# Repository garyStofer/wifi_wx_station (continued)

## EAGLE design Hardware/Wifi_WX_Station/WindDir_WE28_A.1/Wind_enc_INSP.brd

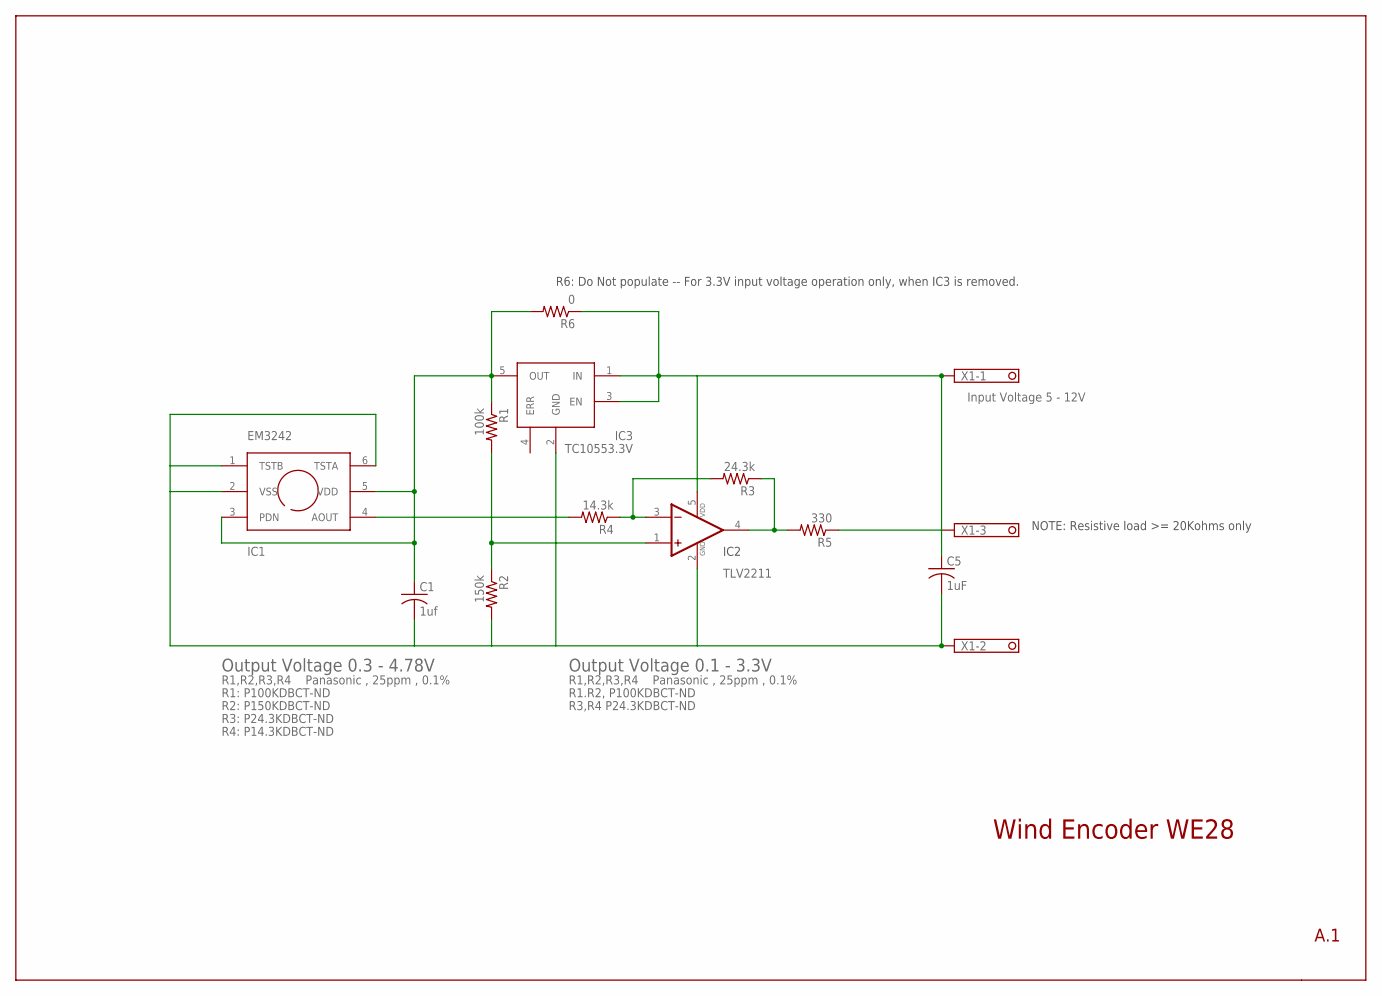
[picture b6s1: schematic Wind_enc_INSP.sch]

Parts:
C1: 1uf; C0805K
C5: 1uF; C0805K
IC1: EM3242; EM3242_SPECIAL
IC2: TLV2211; SOT23-5
IC3: TC10553.3V; SOT23-5
R1: 100k; R0603
R2: 150k; R0603
R3: 24.3k; R0603
R4: 14.3k; R0603
R5: 330; R0603
R6: 0; R0603
X1: 1751251

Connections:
unnamed: C5.1, IC2.5 (VDD), IC3.1 (IN), IC3.3 (EN), R6.1, X1.1
unnamed: C1.2, C5.2, IC1.1 (TSTB), IC1.2 (VSS), IC1.6 (TSTA), IC2.2 (VDD_GND), IC3.2 (GND), R2.2, X1.2
unnamed: R5.1, X1.3
unnamed: IC1.4 (AOUT), R4.2
unnamed: C1.1, IC1.3 (PDN), IC1.5 (VDD), IC3.5 (OUT), R1.1, R6.2
unnamed: IC2.3 (-IN), R3.2, R4.1
unnamed: IC2.4 (OUT), R3.1, R5.2
unnamed: IC2.1 (+IN), R1.2, R2.1

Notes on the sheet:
Wind Encoder WE28
IC2
R6: Do Not populate -- For 3.3V input voltage operation only, when IC3 is removed.
A.1
R1,R2,R3,R4 Panasonic , 25ppm , 0.1%
R2: P150KDBCT-ND
R1: P100KDBCT-ND
R3: P24.3KDBCT-ND
R4: P14.3KDBCT-ND
Output Voltage 0.3 - 4.78V
Input Voltage 5 - 12V
Output Voltage 0.1 - 3.3V
R1,R2,R3,R4 Panasonic , 25ppm , 0.1%
R1.R2, P100KDBCT-ND
R3,R4 P24.3KDBCT-ND
NOTE: Resistive load >= 20Kohms only

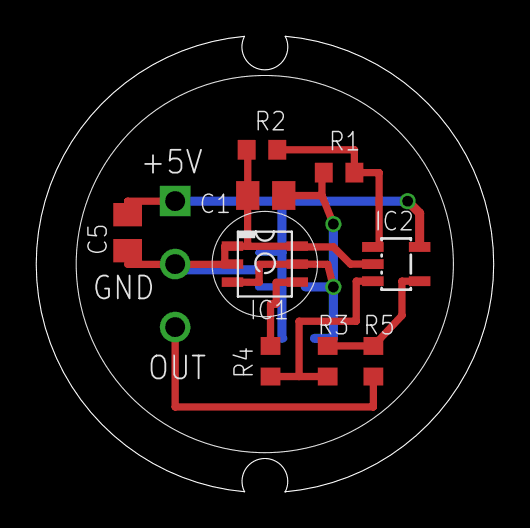
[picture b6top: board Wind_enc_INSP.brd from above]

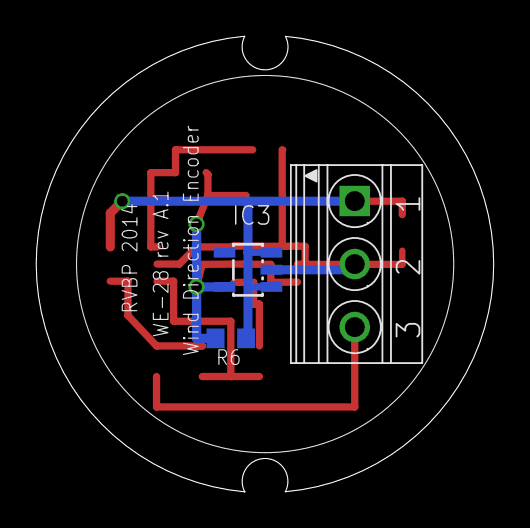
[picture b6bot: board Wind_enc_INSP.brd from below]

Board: 2 copper layers, 25.4 x 25.3 mm, 12 parts (3 on the bottom side), 8 nets.

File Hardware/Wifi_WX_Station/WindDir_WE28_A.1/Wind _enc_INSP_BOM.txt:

BOM for WE28-A1

OP-Amp 	TLV2211		DigiKey 	296-10501-1-ND	 
Encoder EM3242		Digikey  	974-1044-1-ND	 
VR 	TC10553.3V	DigiKey		TC10553.3VCT713CT-ND			 
R1 	100K 0.5% 25ppm 	 
R2	150K 0.1% 25ppm	 
R3	24.3k 0.1% 25ppm	 
R4 	14.3k 0.5% 25ppm	 
R5	330O 2%			 
C1,C2	1 uf/ 16V  			311-1457-1-ND

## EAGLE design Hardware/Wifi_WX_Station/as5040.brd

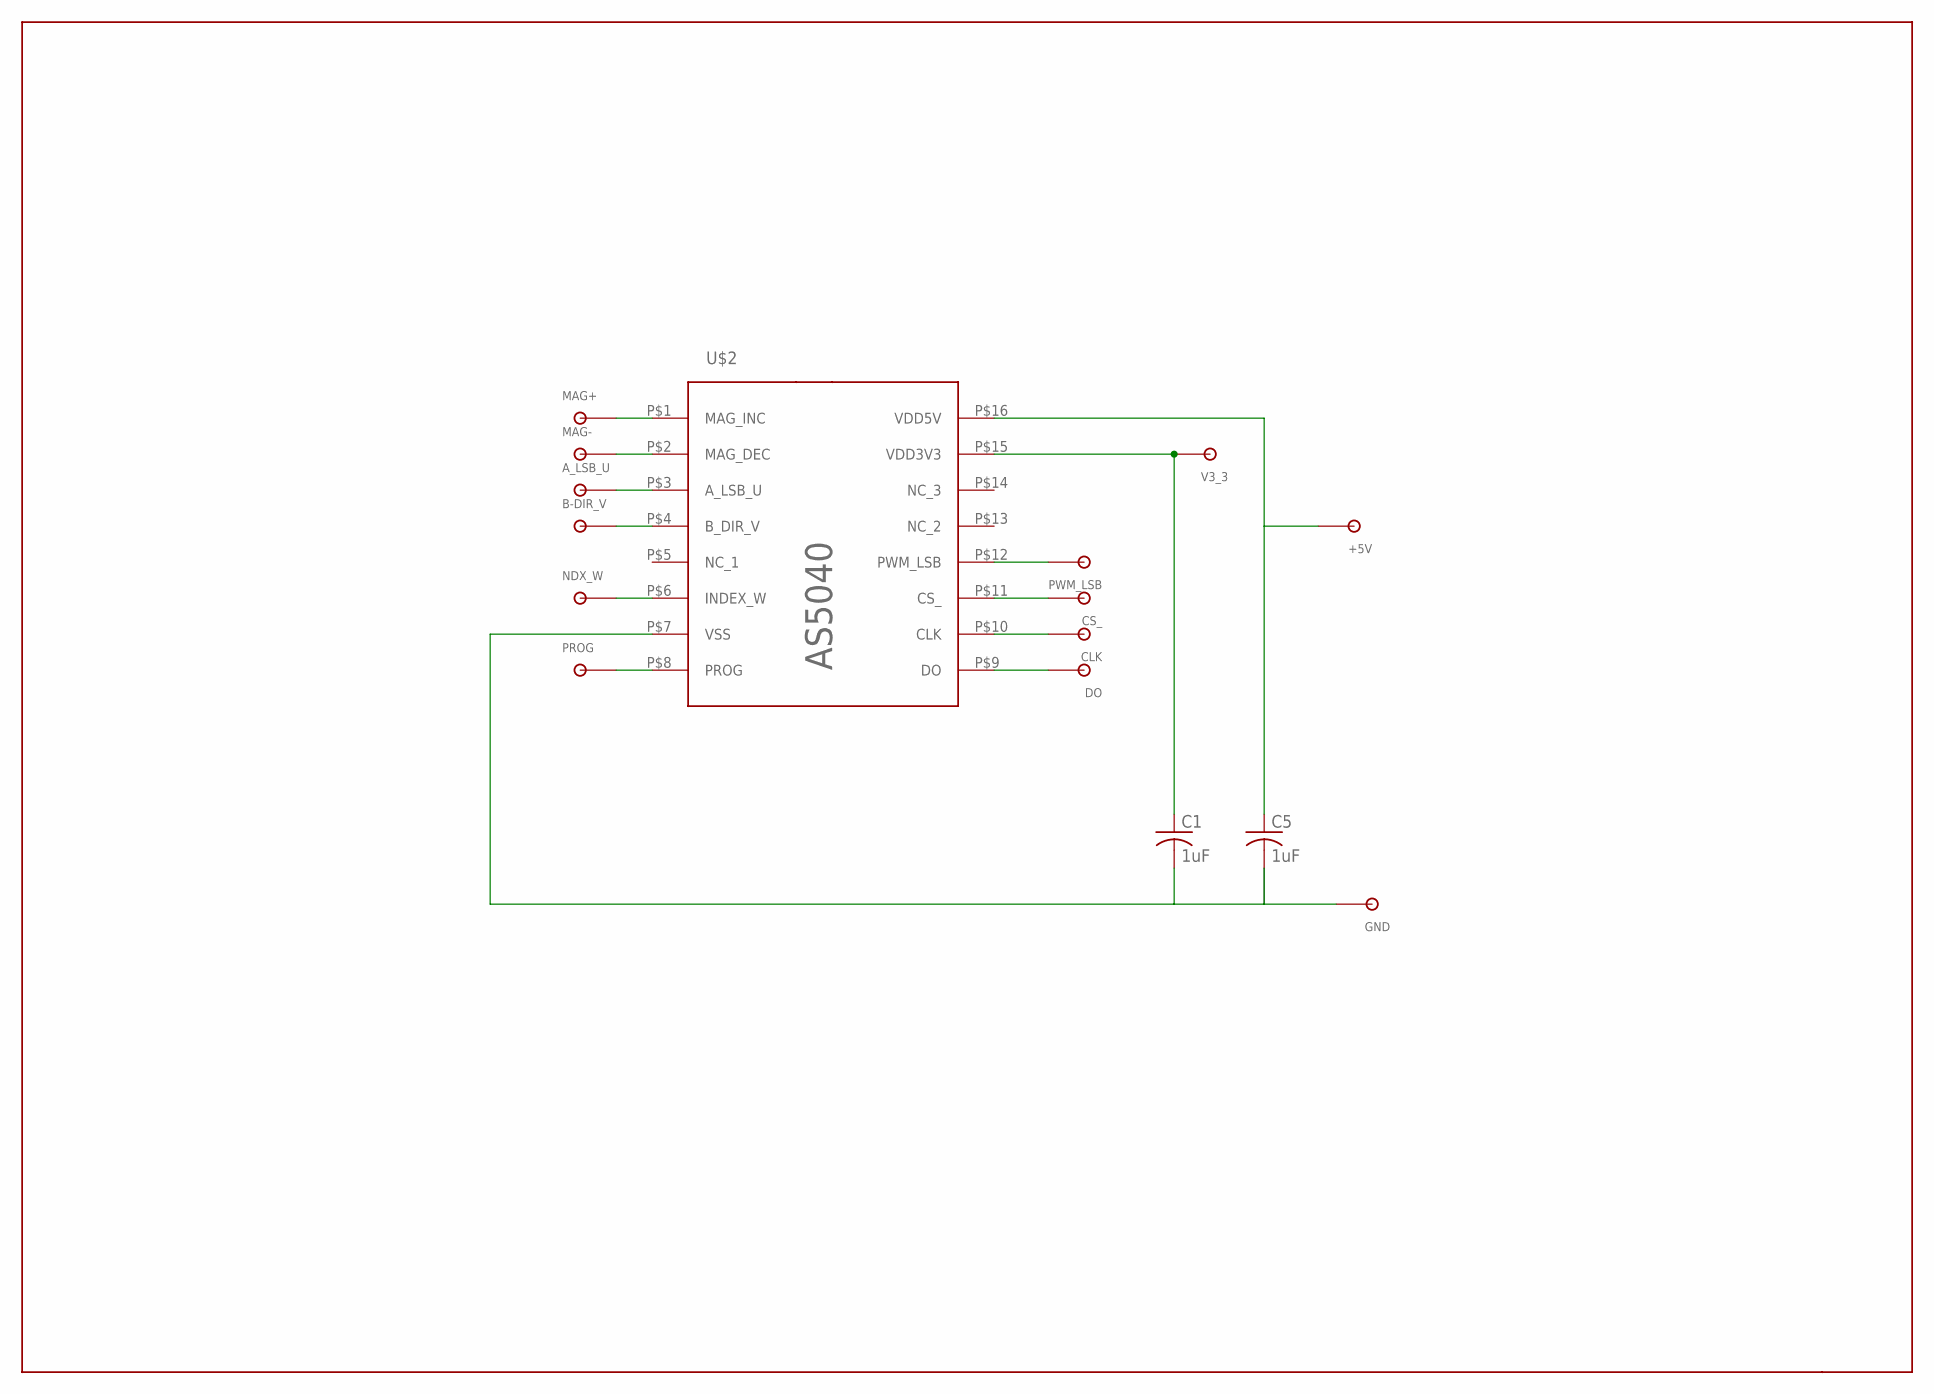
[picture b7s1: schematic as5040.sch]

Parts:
+5V: TPSOL; TP_SOL
A_LSB_U: TPSOL; TP_SOL
B-DIR_V: TPSOL; TP_SOL
C1, C5: 1uF; C0805K
CLK: TPSOL; TP_SOL
CS_: TPSOL; TP_SOL
DO: TPSOL; TP_SOL
GND: TPSOL; TP_SOL
MAG+: TPSOL; TP_SOL
MAG-: TPSOL; TP_SOL
NDX_W: TPSOL; TP_SOL
PROG: TPSOL; TP_SOL
PWM_LSB: TPSOL; TP_SOL
U$2: AS5040; AMS_5040_SPECIAL
V3_3: TPSOL; TP_SOL

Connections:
unnamed: C1.2, C5.2, GND.P$1, U$2.P$7 (VSS)
unnamed: +5V.P$1, C5.1, U$2.P$16 (VDD5V)
unnamed: C1.1, U$2.P$15 (VDD3V3), V3_3.P$1
unnamed: MAG+.P$1, U$2.P$1 (MAG_INC)
unnamed: MAG-.P$1, U$2.P$2 (MAG_DEC)
unnamed: A_LSB_U.P$1, U$2.P$3 (A_LSB_U)
unnamed: B-DIR_V.P$1, U$2.P$4 (B_DIR_V)
unnamed: NDX_W.P$1, U$2.P$6 (INDEX_W)
unnamed: PROG.P$1, U$2.P$8 (PROG)
unnamed: PWM_LSB.P$1, U$2.P$12 (PWM_LSB)
unnamed: CS_.P$1, U$2.P$11 (CS_)
unnamed: CLK.P$1, U$2.P$10 (CLK)
unnamed: DO.P$1, U$2.P$9 (DO)

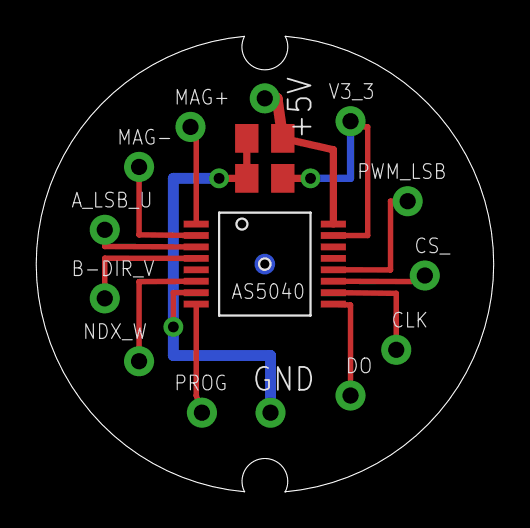
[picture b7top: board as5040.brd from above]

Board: 2 copper layers, 25.4 x 25.3 mm, 16 parts (0 on the bottom side), 13 nets.

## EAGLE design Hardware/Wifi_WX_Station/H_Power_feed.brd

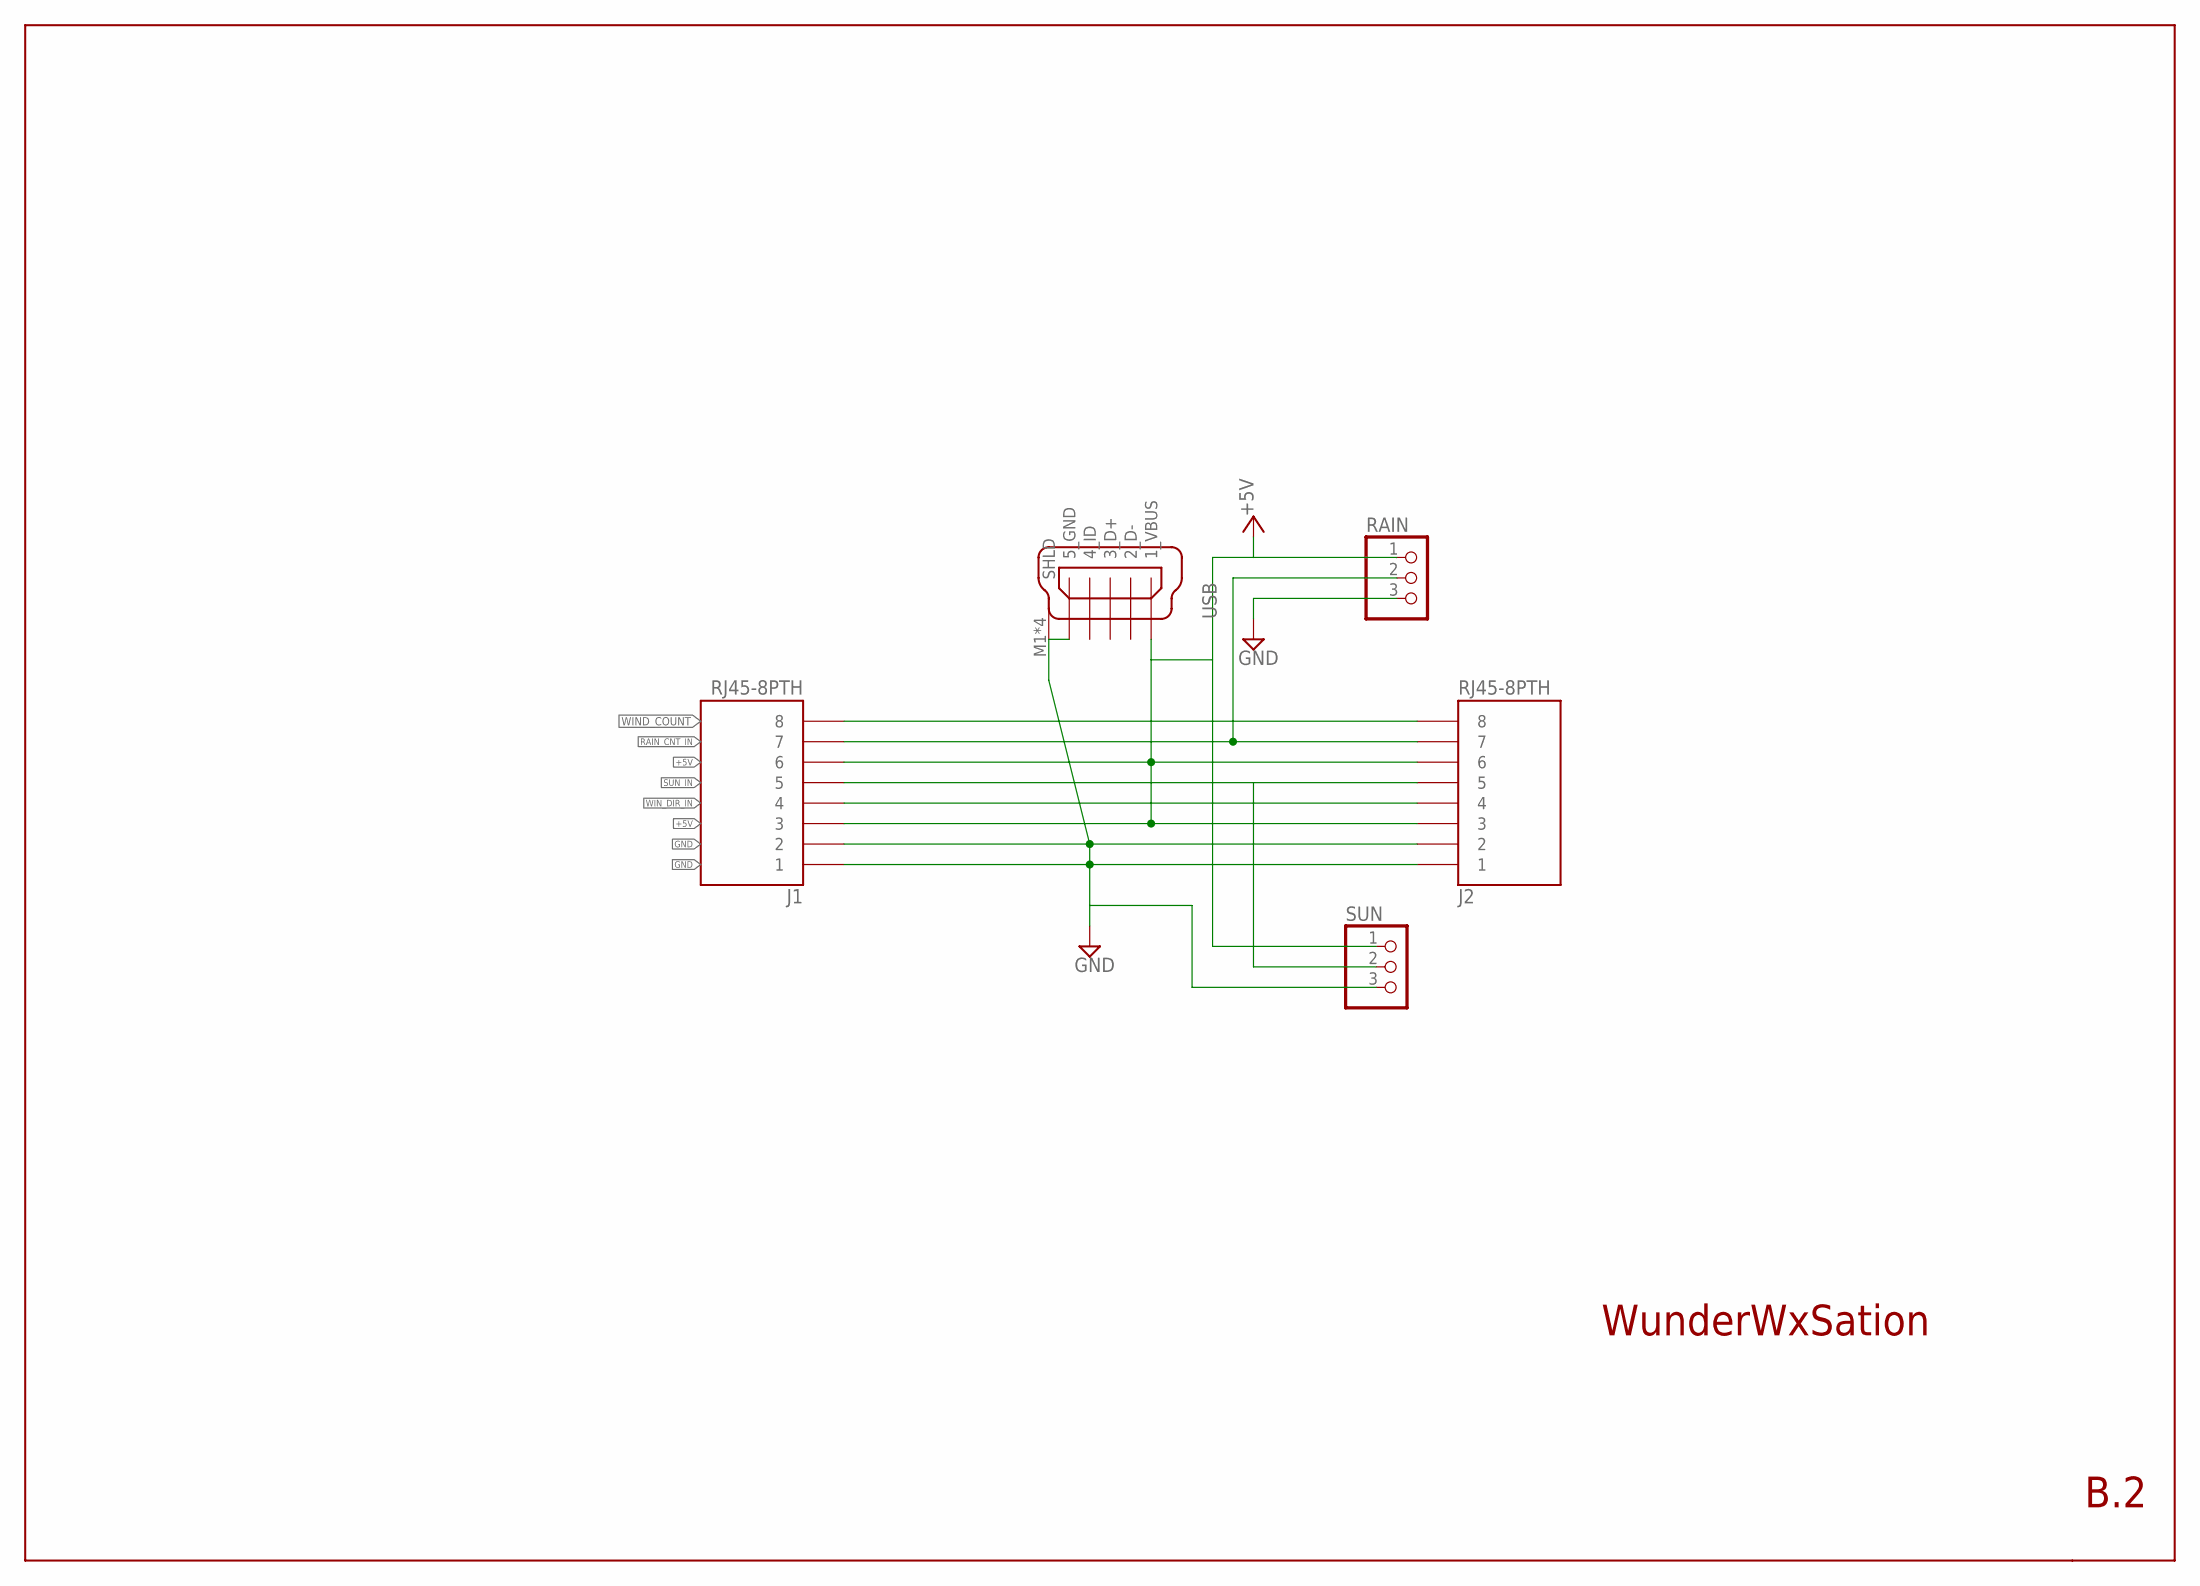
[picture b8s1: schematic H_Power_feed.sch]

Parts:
J1, J2: RJ45-8PTH; RJ45-8
RAIN: PINHD-1X3MOLEX_KK; 1X3_MOLEX_KK
SUN: PINHD-1X3MOLEX_KK; 1X3_MOLEX_KK
USB: MINI-USB-32005-301; 32005-301

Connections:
+5V: J1.3, J1.6, J2.3, J2.6, RAIN.1, SUN.1, USB.1_VBUS
GND: J1.1, J1.2, J2.1, J2.2, RAIN.3, SUN.3, USB.5_USB_GND (5_GND), USB.M1 (SHLD), USB.M2 (SHLD), USB.M3 (SHLD), USB.M4 (SHLD)
RAIN_CNT_IN: J1.7, J2.7, RAIN.2
SUN_IN: J1.5, J2.5, SUN.2
WIND_COUNT: J1.8, J2.8
WIN_DIR_IN: J1.4, J2.4

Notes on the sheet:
WunderWxSation
B.2

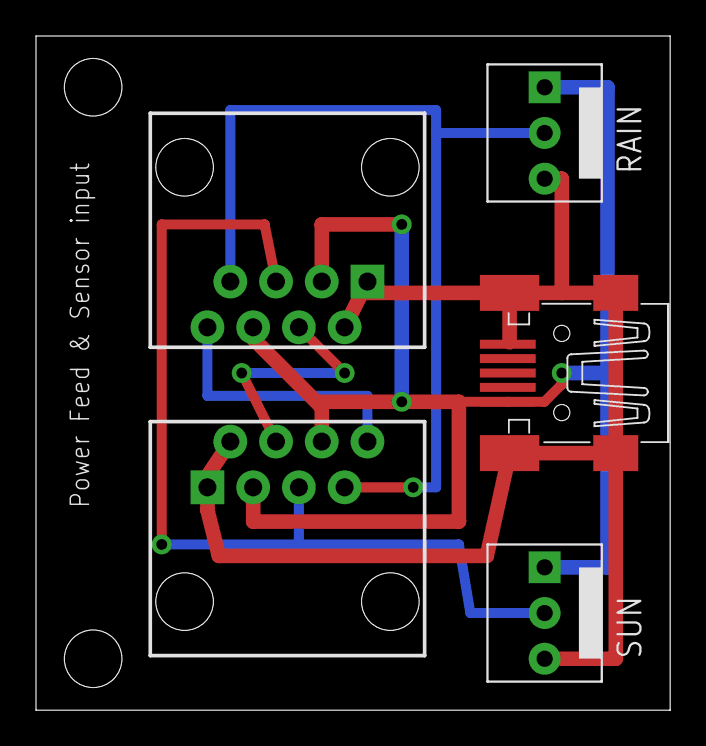
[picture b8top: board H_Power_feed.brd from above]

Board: 2 copper layers, 35.2 x 37.5 mm, 5 parts (0 on the bottom side), 6 nets.

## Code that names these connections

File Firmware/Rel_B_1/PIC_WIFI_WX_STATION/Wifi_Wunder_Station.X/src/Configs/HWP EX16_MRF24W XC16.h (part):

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#define All_LEDS_off()                 LATA = 0
// Momentary push buttons
#define BUTTON0_TRIS		(TRISDbits.TRISD13)	// Ref S4
#define	BUTTON0_IO			(PORTDbits.RD13)
#define BUTTON1_TRIS		(TRISAbits.TRISA7)	// Ref S5;  Note: This is multiplexed with LED7
#define	BUTTON1_IO			(PORTAbits.RA7)
#define BUTTON2_TRIS		(TRISDbits.TRISD7)	// Ref S6
#define	BUTTON2_IO			(PORTDbits.RD7)
#define BUTTON3_TRIS		(TRISDbits.TRISD6)	// Ref S3
#define	BUTTON3_IO			(PORTDbits.RD6)

#define BARO_CS_TRIS   ( TRISGbits.TRISG0)
#define BARO_CS_IO     ( LATGbits.LATG0)
#define UART2TX_TRIS			(TRISFbits.TRISF5)
#define UART2TX_IO			(PORTFbits.RF5)
#define UART2RX_TRIS			(TRISFbits.TRISF4)
#define UART2RX_IO			(PORTFbits.RF4)

//// ENC28J60 I/O pins
//#if defined(__PIC24FJ256GA110__) || defined(__dsPIC33E__)|| defined(__PIC24E__)	// PIC24FJ256GA110 must place the ENC28J60 on SPI2 because PIC rev A3 SCK1 output pin is a PPS input only (fixed on A5, but demos use SPI2 for simplicity)
//	#define ENC_CS_TRIS			(TRISFbits.TRISF12)	// Comment this line out if you are using the ENC424J600/624J600, MRF24W, or other network controller.
//	#define ENC_CS_IO			(LATFbits.LATF12)
//	// SPI SCK, SDI, SDO pins are automatically controlled by the 
//	// PIC24/dsPIC SPI module 
//	#define ENC_SPI_IF			(IFS2bits.SPI2IF)
//	#define ENC_SSPBUF			(SPI2BUF)
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//#else	// SPI1 for all other processors
//	#define ENC_CS_TRIS			(TRISDbits.TRISD14)	// Comment this line out if you are using the ENC424J600/624J600, MRF24W, or other network controller.
//	#define ENC_CS_IO			(LATDbits.LATD14)
//	// SPI SCK, SDI, SDO pins are automatically controlled by the 
//	// PIC24/dsPIC SPI module 
//	#define ENC_SPI_IF			(IFS0bits.SPI1IF)
//	#define ENC_SSPBUF			(SPI1BUF)
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//	#define ENC100_INT_IO				(PORTAbits.RA13)
//#else
//	#define ENC100_INT_TRIS				(TRISEbits.TRISE9)		// INT signal is optional and currently unused in the Microchip TCP/IP Stack.  Leave this pin disconnected and comment out this pin definition if you don't want it.
//	#define ENC100_INT_IO				(PORTEbits.RE9)
//#endif
//#if (ENC100_INTERFACE_MODE >= 1)	// Parallel mode
//	// PSP control signal pinout
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//		// SPI2 CANNOT BE ENABLED WHEN ACCESSING THE ENC624J600 FOR THESE TWO MODES AS THE PINS OVERLAP WITH ADDRESS LINES.
//		#if defined(ENC100_PSP_USE_INDIRECT_RAM_ADDRESSING)	// Only ENC624J600 address pins A0-A8 connected (A9-A14 tied to Vdd)
//			#if defined(__PIC24FJ256GB210__)
//				#define ENC100_INIT_PSP_BIT_BANG()	do{ANSA &= 0xF9E7; ANSB &= 0x3FFF; ANSG &= 0xFCFF;} while(0)		// RE0-RE7, RF12, RD11, RD4, RD5 (AD0-AD7, A5, A8, WR, RD) pins are already digital only pins.
//			#else
//				#define ENC100_INIT_PSP_BIT_BANG()	do{((volatile unsigned char*)&AD1PCFGH)[1] = 0xFF; ((volatile unsigned char*)&AD1PCFGL)[1] |= 0xC0;}while(0)	// Disable AN24-AN31 and AN14-AN15 analog inputs on RE0-RE7 and RB14-RB15 pins (ENCX24J600 AD0-AD7, A1-A0)
//			#endif
//			#define ENC100_SET_ADDR_TRIS_OUT()	do{TRISA &= 0xF9E7; TRISB &= 0x3FFF; TRISFbits.TRISF12 = 0; TRISGbits.TRISG9 = 0; TRISDbits.TRISD11 = 0;}while(0)
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//			#define ENC100_SET_AD_IO(data)		(((volatile unsigned char*)&LATE)[0] = (unsigned char)(data))
//		#else 	// All ENC624J600 address pins A0-A14 connected
//			#if defined(__PIC24FJ256GB210__)
//				#define ENC100_INIT_PSP_BIT_BANG()	do{ANSA &= 0xF9E7; ANSB &= 0x03FF; ANSG &= 0xFCFF;} while(0)		// RE0-RE7, RF12, RD11, RD4, RD5 (AD0-AD7, A5, A14, WR, RD) pins are already digital only pins.
//			#else
//				#define ENC100_INIT_PSP_BIT_BANG()	do{((volatile unsigned char*)&AD1PCFGH)[1] = 0xFF; ((volatile unsigned char*)&AD1PCFGL)[1] |= 0xFC;}while(0)	// Disable AN24-AN31 and AN10-AN15 analog inputs on RE0-RE7 and RB10-RB15 pins (ENCX24J600 AD0-AD7, A1-A0, A13-A10)
//			#endif
//			#define ENC100_SET_ADDR_TRIS_OUT()	do{TRISA &= 0xF9E7; TRISB &= 0x03FF; TRISF &= 0xEFCF; TRISGbits.TRISG9 = 0; TRISDbits.TRISD11 = 0;}while(0)
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//			#define ENC100_WRH_B1SEL_IO			ENC100_SO_WR_B0SEL_EN_IO
//			#define ENC100_SET_AD_TRIS_IN()		do{((volatile unsigned char*)&TRISE)[0] = 0xFF; TRISAbits.TRISA15 = 1; TRISCbits.TRISC13 = 1; TRISD |= 0x30C0; TRISGbits.TRISG0 = 1; TRISGbits.TRISG1 = 1;}while(0)
//			#define ENC100_SET_AD_TRIS_OUT()	do{((volatile unsigned char*)&TRISE)[0] = 0x00; TRISAbits.TRISA15 = 0; TRISCbits.TRISC13 = 0; TRISD &= 0xCF3F; TRISGbits.TRISG0 = 0; TRISGbits.TRISG1 = 0;}while(0)
//			#define ENC100_GET_AD_IOH()			(PORTGbits.RG0 | (PORTGbits.RG1<<1) | (PORTCbits.RC13<<2) | (PORTAbits.RA15<<3) | (PORTDbits.RD12<<4) | (PORTDbits.RD13<<5) | (PORTDbits.RD6<<6) | (PORTDbits.RD7<<7))
//			#define ENC100_GET_AD_IOL()			(((volatile unsigned char*)&PORTE)[0])
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//			#define ENC100_SET_AD_IOL(data)		(((volatile unsigned char*)&LATE)[0] = (unsigned char)(data))
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//			#define ENC100_WRH_B1SEL_IO			ENC100_SO_WR_B0SEL_EN_IO
//			#define ENC100_SET_AD_TRIS_IN()		do{((volatile unsigned char*)&TRISE)[0] = 0xFF; TRISAbits.TRISA15 = 1; TRISCbits.TRISC13 = 1; TRISD |= 0x30C0; TRISGbits.TRISG0 = 1; TRISGbits.TRISG1 = 1;}while(0)
//			#define ENC100_SET_AD_TRIS_OUT()	do{((volatile unsigned char*)&TRISE)[0] = 0x00; TRISAbits.TRISA15 = 0; TRISCbits.TRISC13 = 0; TRISD &= 0xCF3F; TRISGbits.TRISG0 = 0; TRISGbits.TRISG1 = 0;}while(0)
//			#define ENC100_GET_AD_IOH()			(PORTGbits.RG0 | (PORTGbits.RG1<<1) | (PORTCbits.RC13<<2) | (PORTAbits.RA15<<3) | (PORTDbits.RD12<<4) | (PORTDbits.RD13<<5) | (PORTDbits.RD6<<6) | (PORTDbits.RD7<<7))
//			#define ENC100_GET_AD_IOL()			(((volatile unsigned char*)&PORTE)[0])
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//			#define ENC100_SET_AD_IOL(data)		(((volatile unsigned char*)&LATE)[0] = (unsigned char)(data))
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//	#elif ENC100_INTERFACE_MODE == 5 || ENC100_INTERFACE_MODE == 6	// Mutliplexed 8-bit address/data modes
//		#if defined(ENC100_PSP_USE_INDIRECT_RAM_ADDRESSING)	// Only ENCX24J600 address pins AD0-AD8 connected (AD9-AD14 tied to Vdd)
//			#if defined(__PIC24FJ256GB210__)
//				#define ENC100_INIT_PSP_BIT_BANG()	do{ANSB &= 0x7FFF; ANSG &= 0xFEFF;} while(0)		// RE0-RE7, RD11, RD4, RD5 (AD0-AD7, AD8, WR, RD) pins are already digital only pins.  RB15, RG8 (AL, CS) needs to be made digital only.
//			#else
//				#define ENC100_INIT_PSP_BIT_BANG()	do{((volatile unsigned char*)&AD1PCFGH)[1] = 0xFF;}while(0)	// Disable AN24-AN31 analog inputs on RE0-RE7 pins (ENCX24J600 AD0-AD7)
//			#endif
//			#define ENC100_SET_AD_TRIS_IN()		do{((volatile unsigned char*)&TRISE)[0] = 0xFF;}while(0)
//			#define ENC100_SET_AD_TRIS_OUT()	do{((volatile unsigned char*)&TRISE)[0] = 0x00; TRISDbits.TRISD11 = 0;}while(0)
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//			// UART2 CANNOT BE USED OR ENABLED FOR THESE TWO MODES AS THE PINS OVERLAP WITH ADDRESS LINES.
//			#if defined(__PIC24FJ256GB210__)
//				#define ENC100_INIT_PSP_BIT_BANG()	do{ANSB &= 0x43FF; ANSG &= 0xFEFF;} while(0) // Set pins as digital I/Os (not analog).  RD11, RD5, RD4, RE0-RE7, RF4, RF5 are all digital-only pins and therefore no writes to ANSD, ANSE, or ANSF are needed.
//			#else
//				#define ENC100_INIT_PSP_BIT_BANG()	do{AD1PCFGL |= 0x3C00; ((volatile unsigned char*)&AD1PCFGH)[1] = 0xFF;}while(0)	// Disable AN10-AN13 and AN24-AN31 analog inputs on RB10-RB13 and RE0-RE7 pins (ENCX24J600 AD13-AD10 and AD0-AD7)
//			#endif
//			#define ENC100_SET_AD_TRIS_IN()		do{((volatile unsigned char*)&TRISE)[0] = 0xFF;}while(0)
//			#define ENC100_SET_AD_TRIS_OUT()	do{((volatile unsigned char*)&TRISE)[0] = 0x00; TRISFbits.TRISF5 = 0; TRISFbits.TRISF4 = 0; TRISB &= 0x43FF; TRISDbits.TRISD11 = 0;}while(0)
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//		// All ENC624J600 adddress/data pins AD0-AD15 connected (required for 16-bit data, so there is no differentiation for indirect versus direct addressing mode)
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//		#if defined(__PIC24FJ256GB210__)
//			#define ENC100_INIT_PSP_BIT_BANG()	do{ANSBbits.ANSB15 = 0; ANSCbits.ANSC13 = 0; ANSD &= 0xCF0F; ANSGbits.ANSG8 = 0;}while(0)	// Set pins as digital I/Os (not analog).  RA15 and RE0-RE7 are all digital-only pins and therefore no writes to ANSA or ANSE are needed.
//		#else
//			#define ENC100_INIT_PSP_BIT_BANG()	do{((volatile unsigned char*)&AD1PCFGH)[1] = 0xFF;}while(0)	// Disable AN24-AN31 analog inputs on RE0-RE7 pins (ENCX24J600 AD0-AD7)
//		#endif
//		#define ENC100_WRH_B1SEL_TRIS		ENC100_SO_WR_B0SEL_EN_TRIS
//		#define ENC100_WRH_B1SEL_IO			ENC100_SO_WR_B0SEL_EN_IO
//		#define ENC100_SET_AD_TRIS_IN()		do{((volatile unsigned char*)&TRISE)[0] = 0xFF; TRISAbits.TRISA15 = 1; TRISCbits.TRISC13 = 1; TRISD |= 0x30C0; TRISGbits.TRISG0 = 1; TRISGbits.TRISG1 = 1;}while(0)
//		#define ENC100_SET_AD_TRIS_OUT()	do{((volatile unsigned char*)&TRISE)[0] = 0x00; TRISAbits.TRISA15 = 0; TRISCbits.TRISC13 = 0; TRISD &= 0xCF3F; TRISGbits.TRISG0 = 0; TRISGbits.TRISG1 = 0;}while(0)
//		#define ENC100_GET_AD_IOH()			(PORTGbits.RG0 | (PORTGbits.RG1<<1) | (PORTCbits.RC13<<2) | (PORTAbits.RA15<<3) | (PORTDbits.RD12<<4) | (PORTDbits.RD13<<5) | (PORTDbits.RD6<<6) | (PORTDbits.RD7<<7))
//		#define ENC100_GET_AD_IOL()			(((volatile unsigned char*)&PORTE)[0])
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//		#define ENC100_SET_AD_IOL(data)		(((volatile unsigned char*)&LATE)[0] = (unsigned char)(data))
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
// 25LC256 I/O pins
#if defined(__PIC24FJ256GB110__)
	// PIC24FJ256GB110 USB PIM has RD12 pin on Explorer 16 schematic 
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
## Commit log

2013-01-18 Revamped web-interface added Rain reporting changed reporting of dateutc to now
2013-03-04 added support for 256GA008 added -- changed directory TCPIP Stack to TCPIP to eliminate compiler warnings because of space in filename. As delivered to Maker.
2013-03-04 deleted TCPIP Stack directory
2013-03-04 added all the small boards, renamed Wifi module as RH and LH version
2013-03-08 updated BOM with all prices- As Checked in to BATCH PCB
2013-04-25 Wind speed board and base station rework to rev HW 1.2
2013-05-17 added bootloader project and changed main project to load under bootloader
2013-05-17 Added PC bootloader app
2013-09-24 Revision B.1
2013-11-12 added fail safe code for WiFi module crash -- send Reset after 10 minutes changed the I2C bit-rate to slowest possible to accommodate long sensor cable changed the UART configuration menu to switch b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
2013-11-12 added a comment
2013-11-12 changed wording from Passphrase to Password
2013-11-12 changed the PIC config bytes to match that of the WX-Station application Adjusted the link file for reduced code space considering that we are not using AES option for compilation
2013-11-20 Import of PC-Tools
2013-11-20 moved path of DLL reference
2013-11-26 Changed to RJ11 connector for Baro_temp_hyg on base board -- Cleaned up some silk screen stuff Added new RJ11 based Baro_Temp_Hyg board layout
2013-12-03 Changed config bits for 256 chip to reflect the ones used on the 128k version
2013-12-03 added Phantom Config word so that the Bootloader doesn't produce a false verify error. Added some comments
2013-12-03 Added code to deal with the situation when someone removed the I2C sensors from a running system or the I2C communication otherwise fails midstream. Executes a system wide reset.
    Added code to execute a system wide reset in case the WiFi connection can not be established within 10 minutes, or the WiFi adapter crashed.
2013-12-04 added more oytput messages during WiFi connect
2013-12-26 added SILabs Hygrometer board Added frames to the schematics
2014-01-28 Added support for Silabs 7021 hygrometer- Changed and added LED blink and status indication Added metric local web display. Added Density Altitude to local web display
2014-01-28 Release B.1
2014-03-04 changed name of B1_release branch
2014-03-04 Changed commands to USB UART to set device into configuration mode.
2014-03-04 changed the application Icon to rooster. Renamed the project and exe to WX_bootloader ( no GUI) added svn ID keyword to source files
2014-03-04 misspelled ID
2014-03-04 Added SVN keyword ID
2014-03-04 added upload protocols fro CWOP/APRS, WX-bug and PWS
2014-03-04 moved release B1 to tags folder
2014-03-04 Added multiple new boards - H-pwrdist- Insp_Wind_enc, 5040 etc..
2014-03-05 added Makefilegenesia.properties file to ignores
2014-03-05 added page for CWOP
2014-03-15 Added option to use Temp from either Baro or SI7021 Added remote pages for PWS/Weather and WX_bug
2015-01-08 doubled the timeout time that casues a WiFi assertion from .5s to 1 S. This is only used when the stack is used in debug trace mode
2015-01-08 turned off stack debug trace mode
2015-01-08 stripped out spaces from station ID -- ID can not have leading or trailing spaces
2015-01-08 Added connections to CWOP and WOW servers. Changed Wind averaging to accomodate CWOP report time frames
2015-01-08 changes to support WOW and CWOP
2015-01-08 backup
2015-06-30 some makefile changes to the bootloader subproject -- Unclear to what
2015-06-30 added PCB for BOSH PMP180 revised WE28 schemaitc with added text
2015-06-30 removed unversioned files
2015-07-07 added a branch to work on Soil moisture RF sensor stuff
2015-07-07 Added code for RF soil moisture sensors
2015-07-09 Removed more unused files in nbproject directories added a .gitignore file
2015-10-19 added/changed some comments on schematic regarding Wind dir build options
2016-02-11 Modified the RF carrier slightly with longer pads for easier soldering.
2016-02-11 Initialized the RTC clock to all 0's during setup and added date&time to compass.svg This is that in case the NIST connection fails it will display a date of 2000 instead of random dates. Changed the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
    Consolidated the NIST TCIP IP socket buffer with the default one and used it instead.
2016-02-18 Added code so that the system waits for completion of a DHCP operation before anything else accesses the LAN. This is in response to an issue where the networked was accesses with an old, statically 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
    Reverted the NIST state machine back to start up immediately and not have an initial delay to let DHCP complete, since now the system is blocking until DHCP is complete if enabled.
2016-02-18 Ignored un-needed file in the BL
2016-03-01 Changed Primary NIST server to La Grange Oregon
2016-03-02 Updated BOM with Mouser PN's -- Updated Wind-direction DOC and PDF Updated wind dir doc to better reflect the specifications of the new sensor
2016-03-02 Updated to use new MRF24EG module allowing for 802.11g mode communication. Note that most of the changes are in the MPLAB project, enabling the specific mrf24WG version of the files to be compiled. R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
2016-03-02 changed BOM to reflect new MRF24WG module
2016-03-02 moved interrupter wheel .brd into this folder --
2016-03-28 added misc.xml file with entries for lat/lon , time and timezone offset for Randy P
2016-03-28 Added misc.xlm with lat/lon/TZ-offset and time for Randy P
2016-05-17 Modified the rain counting so that each tip of the bucket immediate updates a software counter via interrupt. This allows WX3D software to calculate the instantaneous rain rate. Also change the avera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
2016-12-09 Reverted back to 60 minute summing of rain readings for RainIn parameter. WU specifies RainIn to be the fallen rain in the last 60 minutes, not instant rain rate, not extrapolated rain rate from a sh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
2017-04-04 Removed old Soil Moisture if-defed code Added raw adc10-15 vars to send ADC raw values to http for soil moisture and other use of analog inputs changed html files accordingly by adding a new adcs.htm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
2017-04-04 Changed the default ADC scale factor for adc0-2 to 15V to correspond with the default HW configuration added commentary .c file for soil moisture linearization for Vegetronix VH400 -- code is not inc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
2017-04-10 Reverted the MAC broadcast interval back to 5 seconds from 50. Added new compass.svg file for soil moisture optional build to not display the compass rose, but instead Soil M readings Fixed ADC scali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
2017-04-12 Added the station discovery tool. Java / NetBeans project to locate the WX station on the local network through it's Discovery port 30303 Original source from Microchi, modified to be specific to WX 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
2017-04-21 Added java tool to read and save the analog readings of a station to a .csv file
2017-04-28 changed MPLAB internal project name to indicate old_mrf added more text to how to run the WX_Soilm_Save tool.
2017-07-28 Added output option for RF APRS for use with the Nano APRS modem hardware Added spec sheet for WE28 Wind direction sensor Fixed some spelling mistakes.
2017-09-18 Added some info on sink and drive currents as well as RPM to MPH conversion factors
2017-09-18 two files for UART1 handling with ring buffer etc
2017-09-18 fixed a ifdef -- same fix as in master branch when merging
2017-09-19 Modified the auto save mechanism for the WiFi encrytion key -- MRF24W-G has a connection manager that caused the need for the change,
2017-11-29 added documentation for APRS-RF config
2018-10-29 Added APRS radio power control, Added solar to items reported fixed a few compiler warnings
2019-02-08 additions and changes for APRS based reporting with telemetry reports for battery voltage and snow height & range. Power control for radio.
